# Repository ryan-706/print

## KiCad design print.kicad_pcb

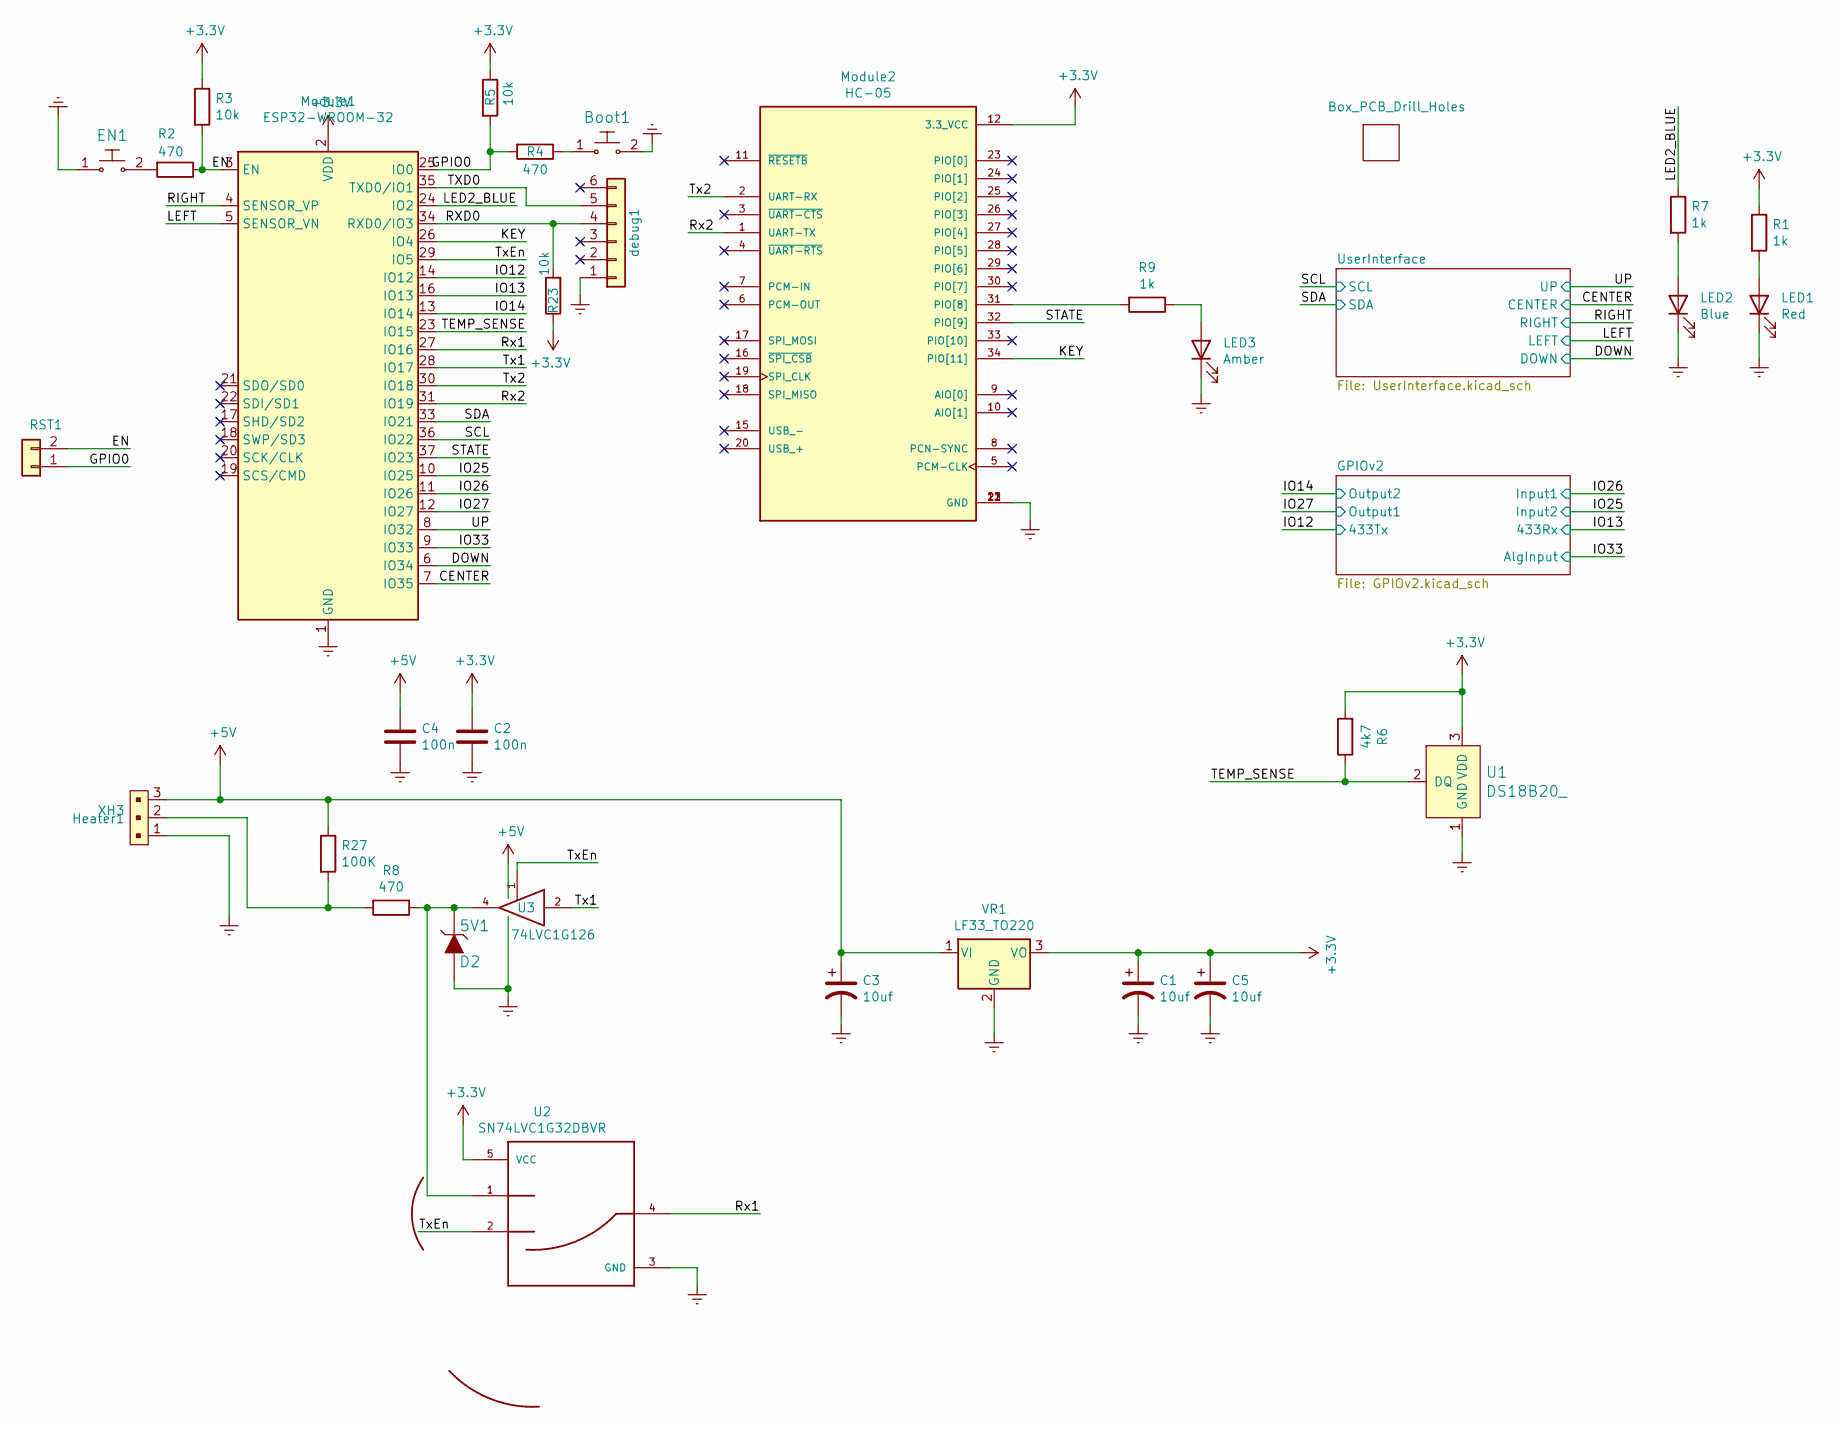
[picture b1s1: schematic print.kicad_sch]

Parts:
Boot1: Tactile_sw_sil; Switch_Tactile_SMD_B3U-1000P; MPN B3U-1000P; Digi-Key_PN SW1020CT-ND
C1, C3, C5: 10uf; C_0805_2012Metric_Pad1.18x1.45mm_HandSolder
C2, C4: 100n; C_0805_2012Metric_Pad1.18x1.45mm_HandSolder
D2: 5V1; SOD-123; MPN MMSZ5231B-7-F; Digi-Key_PN MMSZ5231B-FDICT-ND
EN1: Tactile_sw_sil; Switch_Tactile_SMD_B3U-1000P; MPN B3U-1000P; Digi-Key_PN SW1020CT-ND
Heater1: XH3; PinHeader_1x03_P2.00mm_Vertical; MPN 640456-3; Digi-Key_PN A19470-ND
LED1: Red; Kingbright_APT3216QBC_RED
LED2: Blue; Kingbright_APT3216QBC_RED
LED3: Amber; Kingbright_APT3216QBC_RED
Module1: ESP32-WROOM-32
Module2: HC-05; XCVR_HC-05; PARTREV v1.0
R1, R7, R9: 1k; R_0805_2012Metric_Pad1.20x1.40mm_HandSolder
R2, R4, R8: 470; R_0805_2012Metric_Pad1.20x1.40mm_HandSolder
R3, R5, R23: 10k; R_0805_2012Metric_Pad1.20x1.40mm_HandSolder
R6: 4k7; R_0805_2012Metric_Pad1.20x1.40mm_HandSolder
R27: 100K; R_0805_2012Metric_Pad1.20x1.40mm_HandSolder
RST1: Conn_01x02; PinHeader_1x02_P2.00mm_Vertical
U1: DS18B20_; PinHeader_1x03_P2.00mm_Vertical; MPN DS18B20+; Digi-Key_PN DS18B20+-ND
U2: SN74LVC1G32DBVR; SOT-23-5_HandSoldering; PARTREV V
U3: 74LVC1G126; SOT-23-5_HandSoldering
U7: Box_PCB_Drill_Holes
VR1: LF33_TO220; TO-220-3_Horizontal_TabDown
debug1: Conn_01x06; PinHeader_1x06_P2.00mm_Vertical

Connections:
+3V3: C1.1, C2.1, C5.1, Module1.2 (VDD), Module2.12 (3.3_VCC), R1.1, R3.1, R5.1, R6.2, R23.1, U1.3 (VDD), U2.5 (VCC), VR1.3 (VO); also elsewhere on the board
+5V: C3.1, C4.1, Heater1.3, R27.1, U3.5 (VCC), VR1.1 (VI); also elsewhere on the board
/CENTER: Module1.7 (IO35); also elsewhere on the board
/DOWN: Module1.6 (IO34); also elsewhere on the board
/EN: Module1.3 (EN), R2.1, R3.2, RST1.2
/GPIO0: Module1.25 (IO0), R4.2, R5.2, RST1.1
/IO12: Module1.14 (IO12); also elsewhere on the board
/IO13: Module1.16 (IO13); also elsewhere on the board
/IO14: Module1.13 (IO14); also elsewhere on the board
/IO25: Module1.10 (IO25); also elsewhere on the board
/IO26: Module1.11 (IO26); also elsewhere on the board
/IO27: Module1.12 (IO27); also elsewhere on the board
/IO33: Module1.9 (IO33); also elsewhere on the board
/KEY: Module1.26 (IO4), Module2.34 (PIO[11])
/LED2_BLUE: Module1.24 (IO2), R7.1
/LEFT: Module1.5 (SENSOR_VN); also elsewhere on the board
/RIGHT: Module1.4 (SENSOR_VP); also elsewhere on the board
/RXD0: Module1.34 (RXD0/IO3), R23.2, debug1.4
/Rx1: Module1.27 (IO16), U2.4
/Rx2: Module1.31 (IO19), Module2.1 (UART-TX)
/SCL: Module1.36 (IO22); also elsewhere on the board
/SDA: Module1.33 (IO21); also elsewhere on the board
/STATE: Module1.37 (IO23), Module2.32 (PIO[9])
/TEMP_SENSE: Module1.23 (IO15), R6.1, U1.2 (DQ)
/TXD0: Module1.35 (TXD0/IO1), debug1.5
/Tx1: Module1.28 (IO17), U3.2
/Tx2: Module1.30 (IO18), Module2.2 (UART-RX)
/TxEn: Module1.29 (IO5), U2.2, U3.1
/UP: Module1.8 (IO32); also elsewhere on the board
Earth: Boot1.2, C1.2, C2.2, C3.2, C4.2, C5.2, D2.A, EN1.1, Heater1.1, LED1.1 (K), LED2.1 (K), LED3.1 (K), Module1.1 (GND), Module1.15 (GND), Module1.38 (GND), Module1.39 (GND), Module2.13 (GND), Module2.21 (GND), Module2.22 (GND), U1.1 (GND), U2.3 (GND), U3.3 (GND), VR1.2 (GND), debug1.1; also elsewhere on the board
unnamed: Boot1.1, R4.1
unnamed: D2.K, R8.1, U2.1, U3.4
unnamed: EN1.2, R2.2
unnamed: Heater1.2, R8.2, R27.2
unnamed: LED1.2 (A), R1.2
unnamed: LED2.2 (A), R7.2
unnamed: LED3.2 (A), R9.1
unnamed: Module2.31 (PIO[8]), R9.2

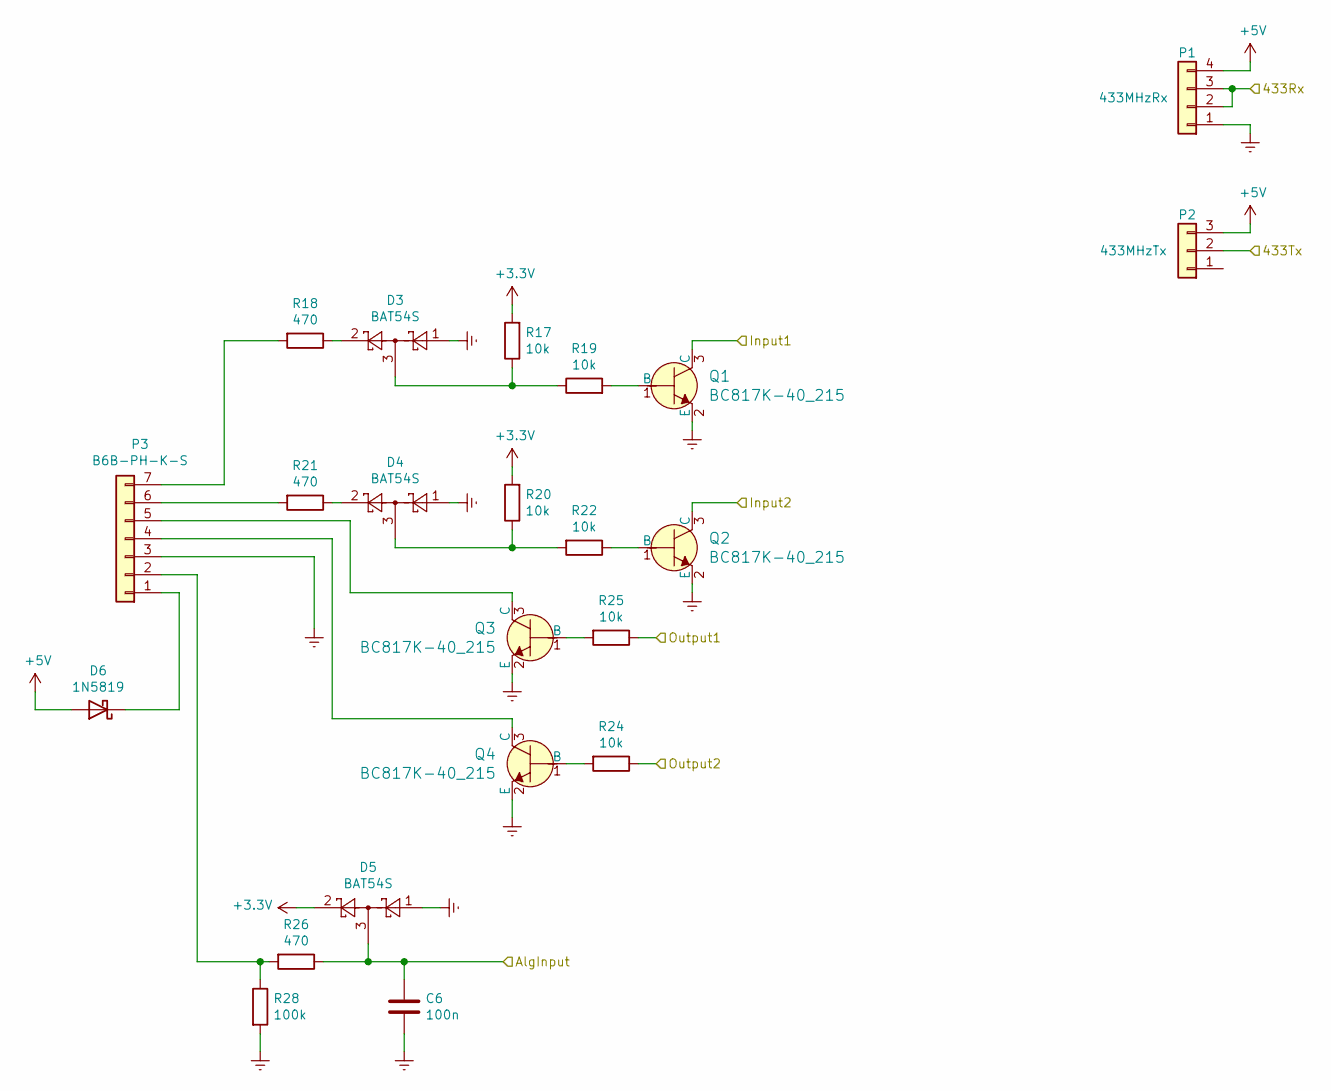
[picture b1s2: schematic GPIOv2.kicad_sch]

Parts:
C6: 100n; C_0805_2012Metric_Pad1.18x1.45mm_HandSolder
D3, D4, D5: BAT54S; SOT-23
D6: 1N5819; D_SOD-123F
P1: 433MHzRx; PinHeader_1x04_P2.00mm_Vertical
P2: 433MHzTx; PinHeader_1x03_P2.00mm_Vertical
P3: B6B-PH-K-S; PinHeader_1x07_P2.00mm_Vertical
Q1, Q2, Q3, Q4: BC817K-40_215; SOT-23-3
R17, R19, R20, R22, R24, R25: 10k; R_0805_2012Metric_Pad1.20x1.40mm_HandSolder
R18, R21, R26: 470; R_0805_2012Metric_Pad1.20x1.40mm_HandSolder
R28: 100k; R_0805_2012Metric_Pad1.20x1.40mm_HandSolder

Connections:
+3V3: D5.2, R17.2, R20.2; also elsewhere on the board
+5V: D6.2 (A), P1.4, P2.3; also elsewhere on the board
/IO12: P2.2; also elsewhere on the board
/IO13: P1.2, P1.3; also elsewhere on the board
/IO14: R24.1; also elsewhere on the board
/IO25: Q2.3 (C); also elsewhere on the board
/IO26: Q1.3 (C); also elsewhere on the board
/IO27: R25.1; also elsewhere on the board
/IO33: C6.1, D5.3, R26.1; also elsewhere on the board
Earth: C6.2, D3.1, D4.1, D5.1, P1.1, P3.3, Q1.2 (E), Q2.2 (E), Q3.2 (E), Q4.2 (E), R28.2; also elsewhere on the board
unnamed: D3.2, R18.1
unnamed: D3.3, R17.1, R19.1
unnamed: D4.2, R21.1
unnamed: D4.3, R20.1, R22.2
unnamed: D6.1 (K), P3.1
unnamed: P3.2, R26.2, R28.1
unnamed: P3.4, Q4.3 (C)
unnamed: P3.5, Q3.3 (C)
unnamed: P3.6, R21.2
unnamed: P3.7, R18.2
unnamed: Q1.1 (B), R19.2
unnamed: Q2.1 (B), R22.1
unnamed: Q3.1 (B), R25.2
unnamed: Q4.1 (B), R24.2

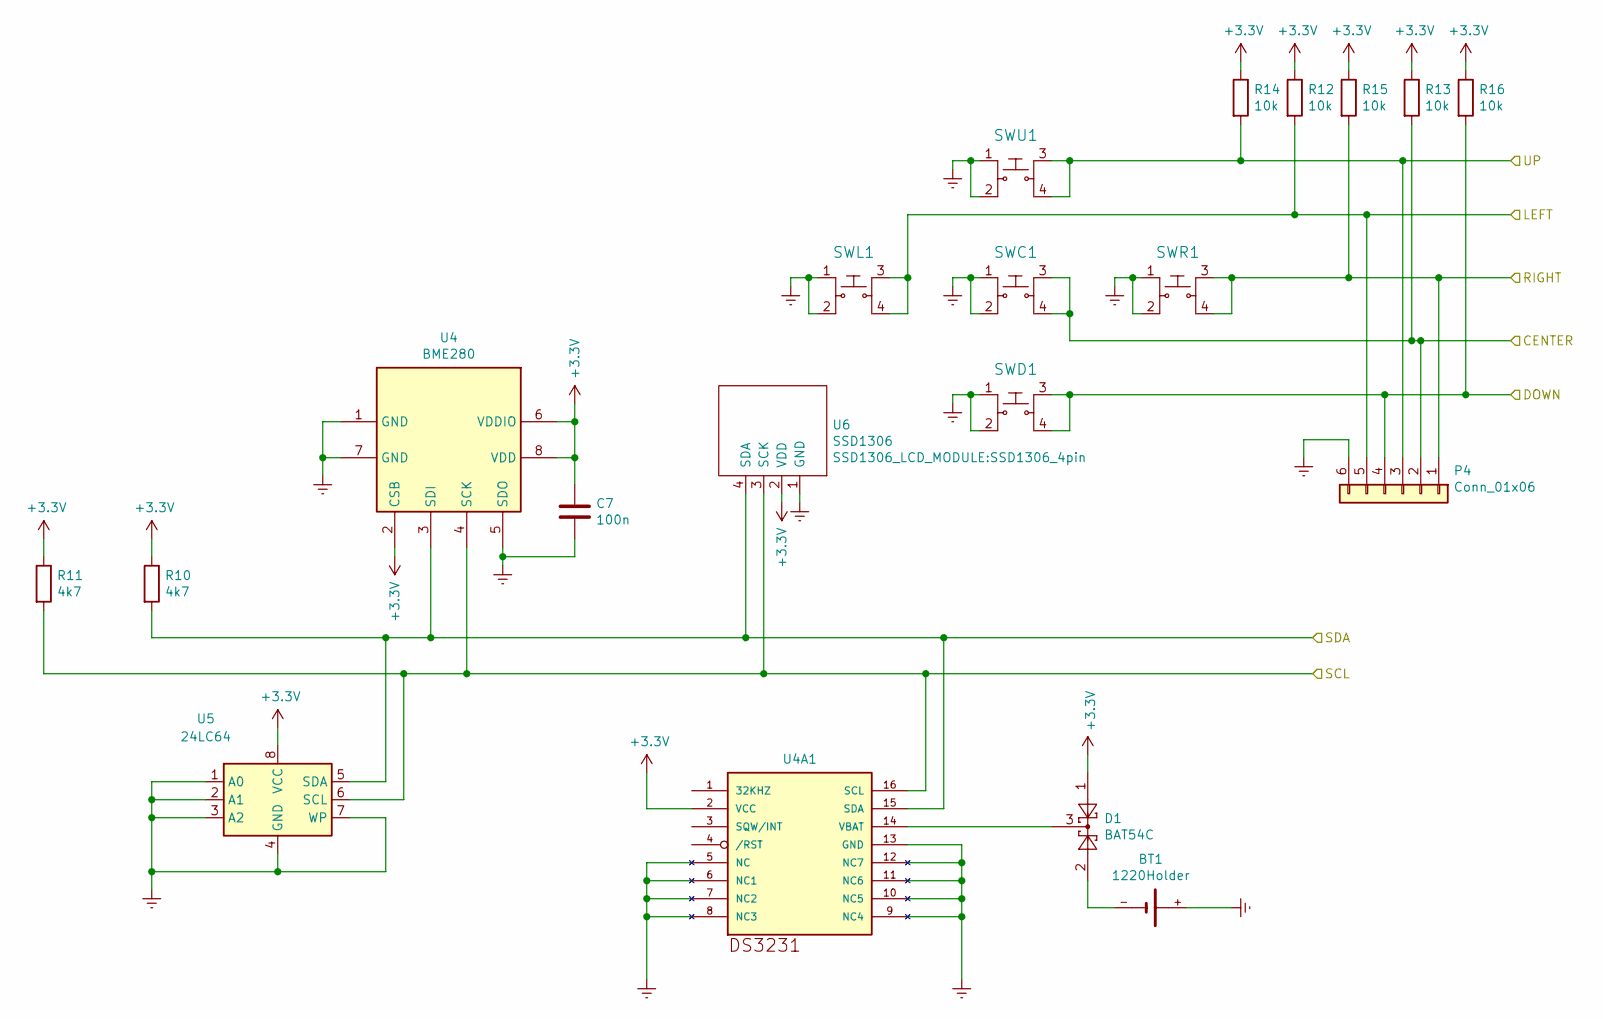
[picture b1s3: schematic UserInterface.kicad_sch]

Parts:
BT1: 1220Holder; S8411-45R_1220BatteryHolder
C7: 100n; C_0805_2012Metric_Pad1.18x1.45mm_HandSolder
D1: BAT54C; SOT-23
P4: Conn_01x06; PinHeader_1x06_P2.00mm_Vertical
R10, R11: 4k7; R_0805_2012Metric_Pad1.20x1.40mm_HandSolder
R12, R13, R14, R15, R16: 10k; R_0805_2012Metric_Pad1.20x1.40mm_HandSolder
SWC1: 1825910-6; tactile_switch; MPN 1825910-6; Digi-Key_PN 450-1650-ND
SWD1: 1825910-6; tactile_switch; MPN 1825910-6; Digi-Key_PN 450-1650-ND
SWL1: 1825910-6; tactile_switch; MPN 1825910-6; Digi-Key_PN 450-1650-ND
SWR1: 1825910-6; tactile_switch; MPN 1825910-6; Digi-Key_PN 450-1650-ND
SWU1: 1825910-6; tactile_switch; MPN 1825910-6; Digi-Key_PN 450-1650-ND
U4: BME280; Bosch_LGA-8_2.5x2.5mm_P0.65mm_ClockwisePinNumbering
U4A1: DS3231
U5: 24LC64
U6: SSD1306; SSD1306_4pin

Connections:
+3V3: C7.1, D1.1, R10.1, R11.1, R12.1, R13.1, R14.1, R15.1, R16.1, U4.2 (CSB), U4.6 (VDDIO), U4.8 (VDD), U4A1.2 (VCC), U5.8 (VCC), U6.2 (VDD); also elsewhere on the board
/CENTER: P4.2, R13.2, SWC1.3, SWC1.4; also elsewhere on the board
/DOWN: P4.4, R16.2, SWD1.3, SWD1.4; also elsewhere on the board
/LEFT: P4.5, R12.2, SWL1.3, SWL1.4; also elsewhere on the board
/RIGHT: P4.1, R15.2, SWR1.3, SWR1.4; also elsewhere on the board
/SCL: R11.2, U4.4 (SCK), U4A1.16 (SCL), U5.6 (SCL), U6.3 (SCK); also elsewhere on the board
/SDA: R10.2, U4.3 (SDI), U4A1.15 (SDA), U5.5 (SDA), U6.4 (SDA); also elsewhere on the board
/UP: P4.3, R14.2, SWU1.3, SWU1.4; also elsewhere on the board
Earth: BT1.+, C7.2, P4.6, SWC1.1, SWC1.2, SWD1.1, SWD1.2, SWL1.1, SWL1.2, SWR1.1, SWR1.2, SWU1.1, SWU1.2, U4.1 (GND), U4.5 (SDO), U4.7 (GND), U4A1.5 (NC), U4A1.6 (NC1), U4A1.7 (NC2), U4A1.8 (NC3), U4A1.9 (NC4), U4A1.10 (NC5), U4A1.11 (NC6), U4A1.12 (NC7), U4A1.13 (GND), U5.1 (A0), U5.2 (A1), U5.3 (A2), U5.4 (GND), U5.7 (WP), U6.1 (GND); also elsewhere on the board
unnamed: BT1.-, D1.2
unnamed: D1.3, U4A1.14 (VBAT)

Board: 2 copper layers, 74 parts (55 on the bottom side), 54 nets, no tracks yet.

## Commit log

2021-03-02 2. Marts 2021
